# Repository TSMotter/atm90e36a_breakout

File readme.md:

Eagle project for a simples breakout board to test ATM90E36A IC.

### Notes:
- This circuit follows the schematic for the 3P4W circuit, present on application note *"Atmel-46104A-SE-M90E36A-ApplicationNote_043014"*.
- Components C22 through C29 are meant to be seen as a generic 0603. If you'll use the chip with Rogowsky coil, you should mount capacitors. If you'll use the chip with CT, you should mount resistors.
- This board served my needs but may need some modifications for your application. **Feel free to download and edit this as you wish.**

### PCB view:
- Top View:

- Botton View:

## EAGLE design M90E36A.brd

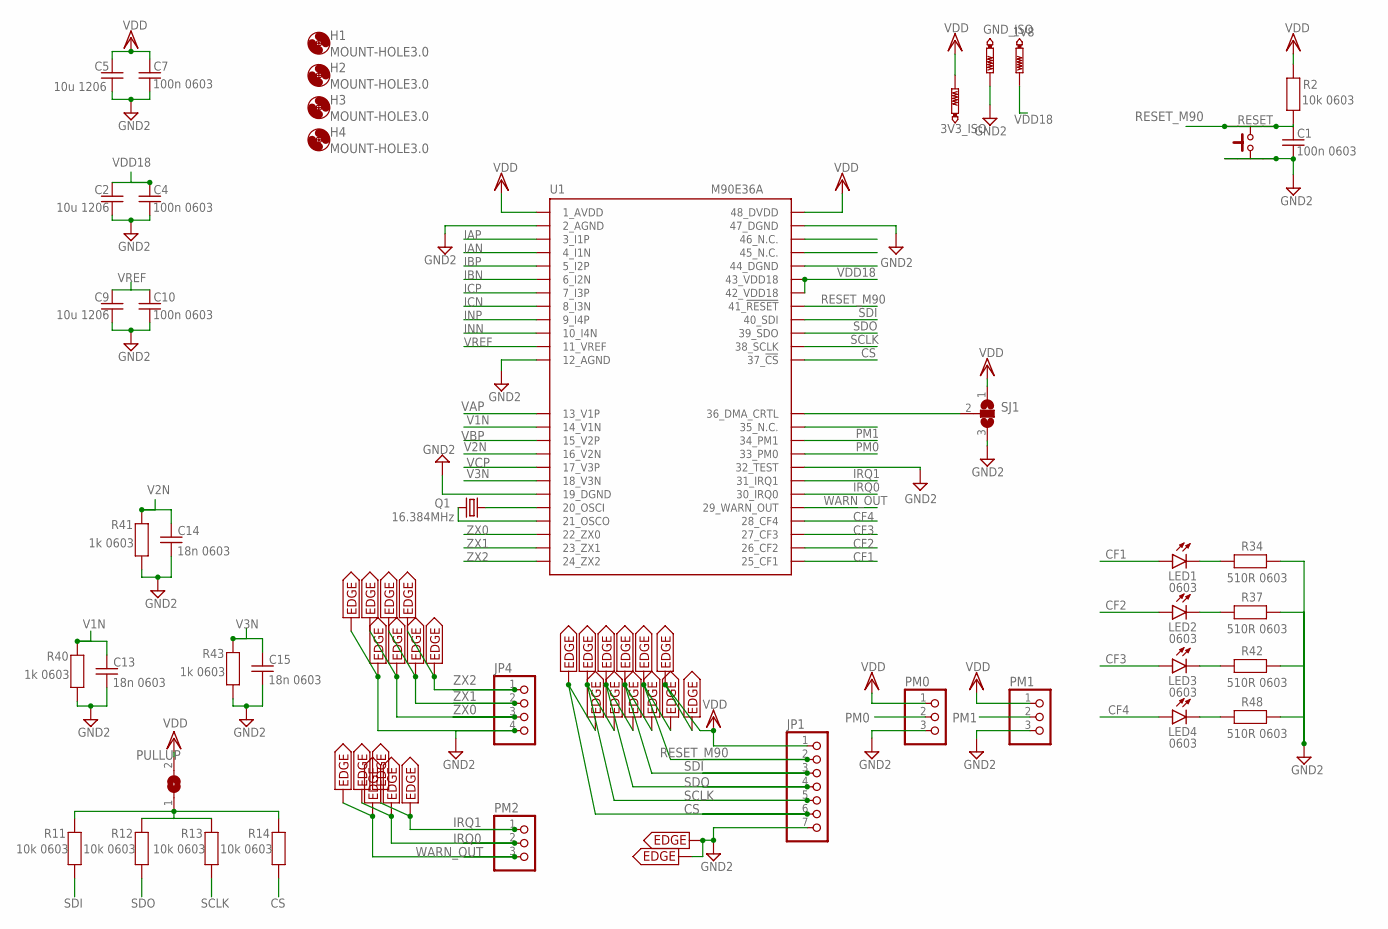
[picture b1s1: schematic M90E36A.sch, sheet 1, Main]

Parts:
1V8, 3V3_ISO: PTR1TP19R; TP19R
C1, C4, C7, C10: 100n 0603; 0603_IMPERIAL
C2, C5, C9: 10u 1206; 1206_IMPERIAL
C13, C14, C15: 18n 0603; 0603_IMPERIAL
GND_ISO: PTR1TP19R; TP19R
H1, H2, H3, H4: MOUNT-HOLE3.0; 3,0
JP1: PINHD-1X7; 1X07
JP4: PINHD-1X4; 1X04
LED1, LED2, LED3, LED4: 0603; CHIPLED_0805
PM0, PM1, PM2: PINHD-1X3; 1X03
PULLUP: SJ
Q1: 16.384MHz; HC49UP
R2, R11, R12, R13, R14: 10k 0603; 0603_IMPERIAL
R34, R37, R42, R48: 510R 0603; 0603_IMPERIAL
R40, R41, R43: 1k 0603; 0603_IMPERIAL
RESET: TACTILE_SWITCHPTH; TACTILE_SWITCH_PTH
SJ1: SJ2W; SJ_2
U1: M90E36A; TQFP-48
U$1, U$2, U$3, U$4, U$5, U$6, U$7, U$8, U$9, U$10, U$11, U$12, U$13, U$14, U$15, U$16, U$17, U$18, U$19, U$20, U$21, U$22, U$23, U$24, U$25, U$26, U$27, U$28: EDGE

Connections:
CF1: LED1.A, U1.P$25 (25_CF1)
CF2: LED2.A, U1.P$26 (26_CF2)
CF3: LED3.A, U1.P$27 (27_CF3)
CF4: LED4.A, U1.P$28 (28_CF4)
CS: JP1.6, R14.P$1, U1.P$37 (37_!CS), U$4.P$1, U$25.P$1
GND2: C1.P$1, C2.P$1, C4.P$1, C5.P$1, C7.P$1, C9.P$1, C10.P$1, C13.P$1, C14.P$1, C15.P$1, GND_ISO.TP, JP1.7, JP4.4, PM0.3, PM1.3, R34.P$2, R37.P$2, R40.P$1, R41.P$1, R42.P$2, R43.P$1, R48.P$2, RESET.P$1 (1), RESET.P$2 (2), SJ1.3, U1.P$2 (2_AGND), U1.P$12 (12_AGND), U1.P$19 (19_DGND), U1.P$32 (32_TEST), U1.P$47 (47_DGND), U$6.P$1, U$10.P$1, U$18.P$1, U$28.P$1; also elsewhere on the board
IAN: U1.P$4 (4_I1N); also elsewhere on the board
IAP: U1.P$3 (3_I1P); also elsewhere on the board
IBN: U1.P$6 (6_I2N); also elsewhere on the board
IBP: U1.P$5 (5_I2P); also elsewhere on the board
ICN: U1.P$8 (8_I3N); also elsewhere on the board
ICP: U1.P$7 (7_I3P); also elsewhere on the board
INN: U1.P$10 (10_I4N); also elsewhere on the board
INP: U1.P$9 (9_I4P); also elsewhere on the board
IRQ0: PM2.2, U1.P$30 (30_IRQ0), U$12.P$1, U$20.P$1
IRQ1: PM2.1, U1.P$31 (31_IRQ1), U$11.P$1, U$19.P$1
unnamed: LED1.C, R34.P$1
unnamed: LED2.C, R37.P$1
unnamed: LED3.C, R42.P$1
unnamed: LED4.C, R48.P$1
unnamed: Q1.2, U1.P$20 (20_OSCI)
unnamed: Q1.1, U1.P$21 (21_OSCO)
unnamed: PULLUP.1, R11.P$2, R12.P$2, R13.P$2, R14.P$2
unnamed: SJ1.2, U1.P$36 (36_DMA_CRTL)
PM0: PM0.2, U1.P$33 (33_PM0)
PM1: PM1.2, U1.P$34 (34_PM1)
RESET_M90: C1.P$2, JP1.2, R2.P$1, RESET.P$3 (3), RESET.P$4 (4), U1.P$41 (41_!RESET), U$14.P$1, U$27.P$1
SCLK: JP1.5, R13.P$1, U1.P$38 (38_SCLK), U$3.P$1, U$24.P$1
SDI: JP1.3, R11.P$1, U1.P$40 (40_SDI), U$1.P$1, U$22.P$1
SDO: JP1.4, R12.P$1, U1.P$39 (39_SDO), U$2.P$1, U$23.P$1
V1N: C13.P$2, R40.P$2, U1.P$14 (14_V1N)
V2N: C14.P$2, R41.P$2, U1.P$16 (16_V2N)
V3N: C15.P$2, R43.P$2, U1.P$18 (18_V3N)
VAP: U1.P$13 (13_V1P); also elsewhere on the board
VBP: U1.P$15 (15_V2P); also elsewhere on the board
VCP: U1.P$17 (17_V3P); also elsewhere on the board
VDD: 3V3_ISO.TP, C5.P$2, C7.P$2, JP1.1, PM0.1, PM1.1, PULLUP.2, R2.P$2, SJ1.1, U1.P$1 (1_AVDD), U1.P$48 (48_DVDD), U$5.P$1, U$26.P$1; also elsewhere on the board
VDD18: 1V8.TP, C2.P$2, C4.P$2, U1.P$42 (42_VDD18), U1.P$43 (43_VDD18)
VREF: C9.P$2, C10.P$2, U1.P$11 (11_VREF)
WARN_OUT: PM2.3, U1.P$29 (29_WARN_OUT), U$13.P$1, U$21.P$1
ZX0: JP4.3, U1.P$22 (22_ZX0), U$9.P$1, U$17.P$1
ZX1: JP4.2, U1.P$23 (23_ZX1), U$8.P$1, U$16.P$1
ZX2: JP4.1, U1.P$24 (24_ZX2), U$7.P$1, U$15.P$1

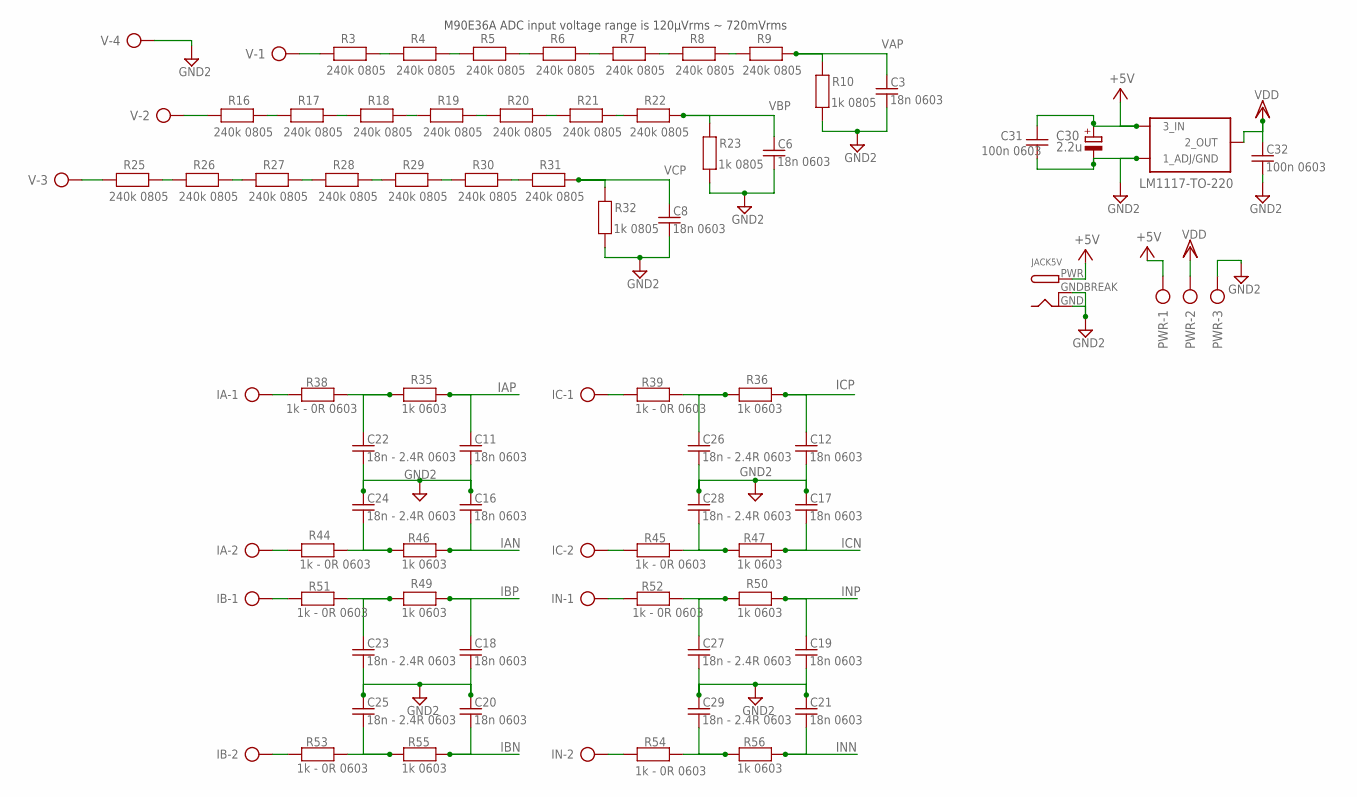
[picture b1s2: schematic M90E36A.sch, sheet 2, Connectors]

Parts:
C3, C6, C8, C11, C12, C16, C17, C18, C19, C20, C21: 18n 0603; 0603_IMPERIAL
C22, C23, C24, C25, C26, C27, C28, C29: 18n - 2.4R 0603; 0603_IMPERIAL
C30: 2.2u; E2,5-5
C31, C32: 100n 0603; 0603_IMPERIAL
IA: AK500/2
IB: AK500/2
IC: AK500/2
IN: AK500/2
JACK5V: DCBARRELPTH; DCJACK_2MM_PTH
PWR: AK500/3
R3, R4, R5, R6, R7, R8, R9, R16, R17, R18, R19, R20, R21, R22, R25, R26, R27, R28, R29, R30, R31: 240k 0805; 0805_IMPERIAL
R10, R23, R32: 1k 0805; 0805_IMPERIAL
R35, R36, R46, R47, R49, R50, R55, R56: 1k 0603; 0603_IMPERIAL
R38, R39, R44, R45, R51, R52, R53, R54: 1k - 0R 0603; 0603_IMPERIAL
U3: LM1117-TO-220; TO-220
V: AK500/4

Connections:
+5V: C30.+, C31.P$2, JACK5V.PWR, PWR.1, U3.3 (3_IN)
GND2: C3.P$1, C6.P$1, C8.P$1, C11.P$1, C12.P$1, C16.P$2, C17.P$2, C18.P$1, C19.P$1, C20.P$2, C21.P$2, C22.P$1, C23.P$1, C24.P$2, C25.P$2, C26.P$1, C27.P$1, C28.P$2, C29.P$2, C30.-, C31.P$1, C32.P$1, JACK5V.GND, JACK5V.GNDBREAK, PWR.3, R10.P$1, R23.P$1, R32.P$1, U3.1 (1_ADJ/GND), V.4; also elsewhere on the board
IAN: C16.P$1, R46.P$2; also elsewhere on the board
IAP: C11.P$2, R35.P$2; also elsewhere on the board
IBN: C20.P$1, R55.P$2; also elsewhere on the board
IBP: C18.P$2, R49.P$2; also elsewhere on the board
ICN: C17.P$1, R47.P$2; also elsewhere on the board
ICP: C12.P$2, R36.P$2; also elsewhere on the board
INN: C21.P$1, R56.P$2; also elsewhere on the board
INP: C19.P$2, R50.P$2; also elsewhere on the board
unnamed: R3.P$2, R4.P$1
unnamed: R4.P$2, R5.P$1
unnamed: R5.P$2, R6.P$1
unnamed: R6.P$2, R7.P$1
unnamed: R7.P$2, R8.P$1
unnamed: R8.P$2, R9.P$1
unnamed: R3.P$1, V.1
unnamed: R16.P$2, R17.P$1
unnamed: R17.P$2, R18.P$1
unnamed: R18.P$2, R19.P$1
unnamed: R19.P$2, R20.P$1
unnamed: R20.P$2, R21.P$1
unnamed: R21.P$2, R22.P$1
unnamed: R25.P$2, R26.P$1
unnamed: R26.P$2, R27.P$1
unnamed: R27.P$2, R28.P$1
unnamed: R28.P$2, R29.P$1
unnamed: R29.P$2, R30.P$1
unnamed: R30.P$2, R31.P$1
unnamed: R16.P$1, V.2
unnamed: R25.P$1, V.3
unnamed: IA.2, R44.P$1
unnamed: C24.P$1, R44.P$2, R46.P$1
unnamed: IC.1, R39.P$1
unnamed: C26.P$2, R36.P$1, R39.P$2
unnamed: IA.1, R38.P$2
unnamed: C22.P$2, R35.P$1, R38.P$1
unnamed: IC.2, R45.P$2
unnamed: C28.P$1, R45.P$1, R47.P$1
unnamed: IB.1, R51.P$2
unnamed: C23.P$2, R49.P$1, R51.P$1
unnamed: IB.2, R53.P$2
unnamed: C25.P$1, R53.P$1, R55.P$1
unnamed: IN.1, R52.P$2
unnamed: C27.P$2, R50.P$1, R52.P$1
unnamed: IN.2, R54.P$2
unnamed: C29.P$1, R54.P$1, R56.P$1
VAP: C3.P$2, R9.P$2, R10.P$2; also elsewhere on the board
VBP: C6.P$2, R22.P$2, R23.P$2; also elsewhere on the board
VCP: C8.P$2, R31.P$2, R32.P$2; also elsewhere on the board
VDD: C32.P$2, PWR.2, U3.2 (2_OUT); also elsewhere on the board

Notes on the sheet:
M90E36A ADC input voltage range is 120μVrms ~ 720mVrms

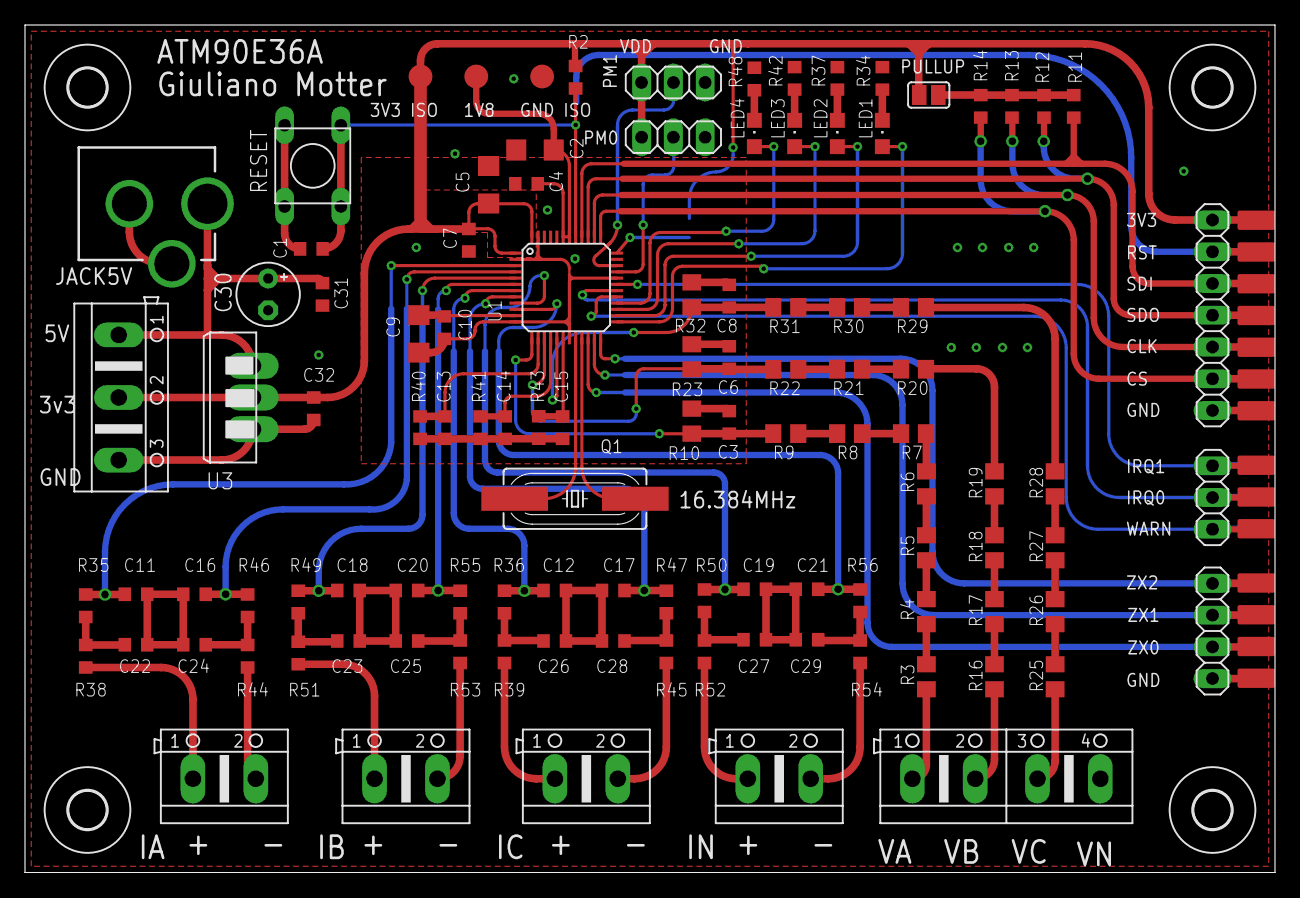
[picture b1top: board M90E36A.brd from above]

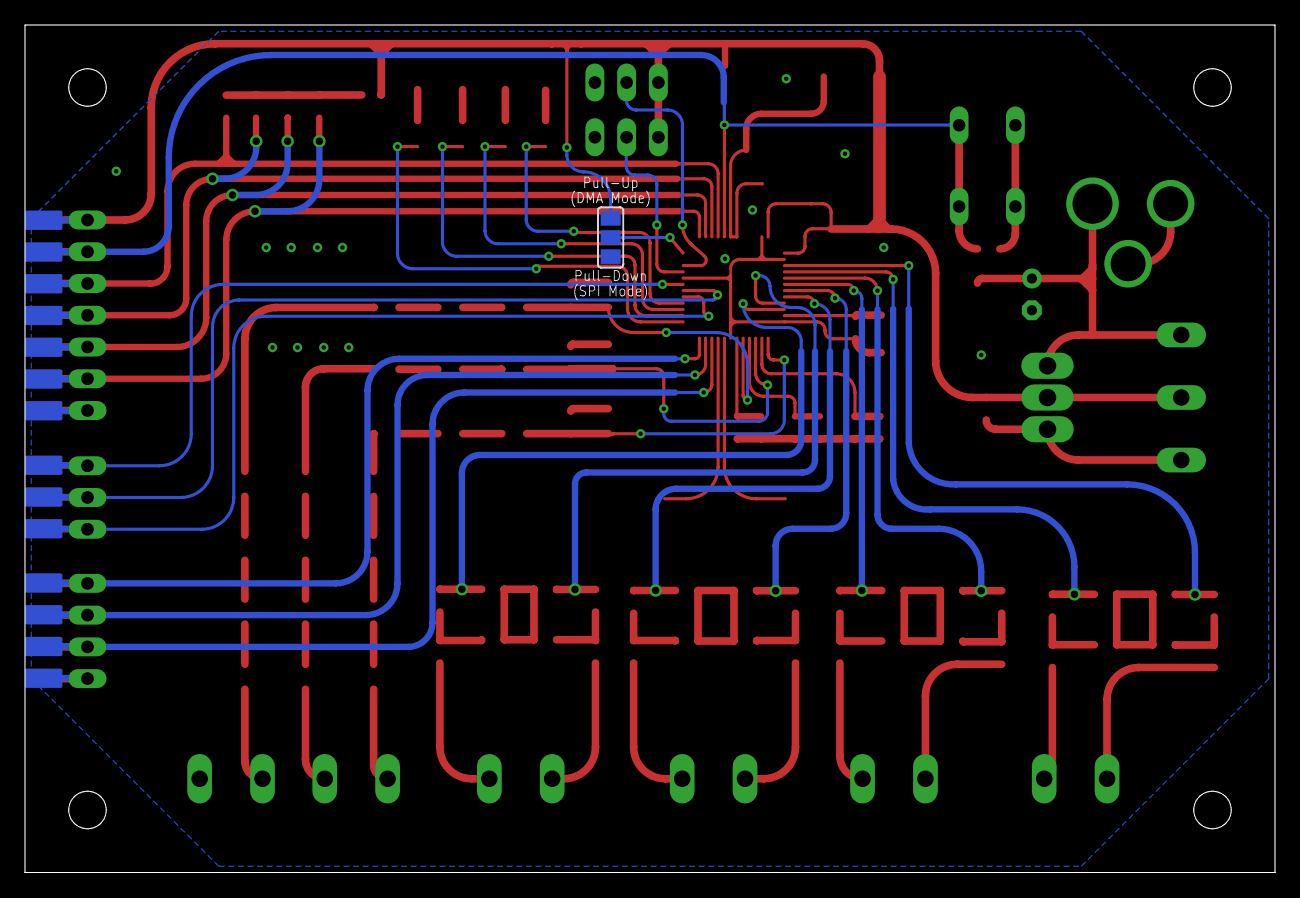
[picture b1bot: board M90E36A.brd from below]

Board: 2 copper layers, 100.0 x 67.8 mm, 141 parts (15 on the bottom side), 81 nets.

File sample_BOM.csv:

"Qty";"Value";"Device";"Package";"Parts";"Description";"FABRICANTE";"MF";"MPN";"OC_FARNELL";"OC_NEWARK";"PARTNUMBER";"POPULARITY";"SPICEPREFIX";"TIPO";"TP_SIGNAL_NAME";
"4";"";"AK500/2";"AK500/2";"IA, IB, IC, IN";"CONNECTOR";"";"";"";"unknown";"unknown";"";"";"";"";"";
"1";"";"AK500/3";"AK500/3";"PWR";"CONNECTOR";"";"";"";"unknown";"unknown";"";"";"";"";"";
"1";"";"AK500/4";"AK500/4";"V";"CONNECTOR";"";"";"";"unknown";"unknown";"";"";"";"";"";
"1";"";"DCBARRELPTH";"DCJACK_2MM_PTH";"JACK5V";"2.0mm DC Barrel Jack";"";"";"";"";"";"";"";"";"";"";
"3";"";"PINHD-1X3";"1X03";"PM0, PM1, PM2";"PIN HEADER";"";"";"";"";"";"";"";"";"";"";
"1";"";"PINHD-1X4";"1X04";"JP4";"PIN HEADER";"";"";"";"";"";"";"";"";"";"";
"1";"";"PINHD-1X7";"1X07";"JP1";"PIN HEADER";"";"";"";"";"";"";"";"";"";"";
"1";"";"SJ";"SJ";"PULLUP";"SMD solder JUMPER";"";"";"";"";"";"";"";"";"";"";
"1";"";"SJ2W";"SJ_2";"SJ1";"SMD solder JUMPER";"";"";"";"";"";"";"7";"";"";"";
"1";"";"TACTILE_SWITCHPTH";"TACTILE_SWITCH_PTH";"RESET";"Chave Tactil-Switch";"METALTEX";"";"";"";"";"A06";"";"";"BOTAO";"";
"4";"0603";"LEDCHIPLED_0805";"CHIPLED_0805";"LED1, LED2, LED3, LED4";"LED";"";"";"";"";"";"";"";"";"";"";
"6";"100n 0603";"C0603";"0603_IMPERIAL";"C1, C4, C7, C10, C31, C32";"Capacitor cerâmico SMD (C0603)";"";"";"";"";"";"";"";"";"CAPACITOR";"";
"5";"10k 0603";"R0603";"0603_IMPERIAL";"R2, R11, R12, R13, R14";"Resistor SMD (R0603)";"";"";"";"";"";"";"";"";"RESISTOR";"";
"3";"10u 1206";"C1206";"1206_IMPERIAL";"C2, C5, C9";"Capacitor SMD (C1206)";"";"";"";"";"";"";"";"";"CAPACITOR";"";
"1";"16.384MHz";"CRYSTALHC49UP";"HC49UP";"Q1";"CRYSTAL";"";"";"";"unknown";"unknown";"";"";"";"";"";
"8";"18n - 2.4R 0603";"C0603";"0603_IMPERIAL";"C22, C23, C24, C25, C26, C27, C28, C29";"Capacitor cerâmico SMD (C0603)";"";"";"";"";"";"";"";"";"CAPACITOR";"";
"14";"18n 0603";"C0603";"0603_IMPERIAL";"C3, C6, C8, C11, C12, C13, C14, C15, C16, C17, C18, C19, C20, C21";"Capacitor cerâmico SMD (C0603)";"";"";"";"";"";"";"";"";"CAPACITOR";"";
"8";"1k - 0R 0603";"R0603";"0603_IMPERIAL";"R38, R39, R44, R45, R51, R52, R53, R54";"Resistor SMD (R0603)";"";"";"";"";"";"";"";"";"RESISTOR";"";
"11";"1k 0603";"R0603";"0603_IMPERIAL";"R35, R36, R40, R41, R43, R46, R47, R49, R50, R55, R56";"Resistor SMD (R0603)";"";"";"";"";"";"";"";"";"RESISTOR";"";
"3";"1k 0805";"R0805";"0805_IMPERIAL";"R10, R23, R32";"Resistor SMD R0805";"";"";"";"";"";"";"";"";"RESISTOR";"";
"1";"2.2u";"CPOL-EUE2.5-5";"E2,5-5";"C30";"POLARIZED CAPACITOR, European symbol";"";"";"";"";"";"";"";"C";"";"";
"21";"240k 0805";"R0805";"0805_IMPERIAL";"R3, R4, R5, R6, R7, R8, R9, R16, R17, R18, R19, R20, R21, R22, R25, R26, R27, R28, R29, R30, R31";"Resistor SMD R0805";"";"";"";"";"";"";"";"";"RESISTOR";"";
"4";"510R 0603";"R0603";"0603_IMPERIAL";"R34, R37, R42, R48";"Resistor SMD (R0603)";"";"";"";"";"";"";"";"";"RESISTOR";"";
"28";"EDGE";"EDGE";"EDGE";"U$1, U$2, U$3, U$4, U$5, U$6, U$7, U$8, U$9, U$10, U$11, U$12, U$13, U$14, U$15, U$16, U$17, U$18, U$19, U$20, U$21, U$22, U$23, U$24, U$25, U$26, U$27, U$28";"";"";"";"";"";"";"";"";"";"";"";
"1";"LM1117-TO-220";"LM1117-TO-220";"TO-220";"U3";"";"";"";"";"";"";"";"";"";"";"";
"1";"M90E36A";"M90E36A";"TQFP-48";"U1";"Poly-Phase High-Performance Energy Metering IC (TQFP48)";"ATMEL";"";"";"";"";"ATM90E36A-AU-Y";"";"";"CIRCUITO INTEGRADO";"";
"4";"MOUNT-HOLE3.0";"MOUNT-HOLE3.0";"3,0";"H1, H2, H3, H4";"MOUNTING HOLE with drill center marker";"";"";"";"";"";"";"";"";"";"";
"3";"PTR1TP19R";"PTR1TP19R";"TP19R";"1V8, 3V3_ISO, GND_ISO";"TEST PIN";"";"";"";"";"";"";"";"";"";"";

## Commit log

2021-10-02 Add readme
